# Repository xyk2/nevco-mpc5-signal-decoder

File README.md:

### Extended documentation at https://xy-kao.com/projects/reverse-engineering-a-serial-scoreboard-protocol-nevco-mpc-5/

### Folders
- *`atmega328_MPC_5_signal_generator`* - replicates a signal from the MPC-5
- *`attiny85_multivibrator`* - microcontroller based multivibrator (1MHz)
- *`logic_analyzer_vcd_dumps`* - dumps from the logic analyzer, used to find correct bit positions in bitstream
- *`MPC-5_decoder_schematic`* - schematic diagram for the circuitry
- *`oscilloscope_screenshots`* - screenshots from the oscilloscope
- *`teensy_decoder`* - primary microcontroller to interpret bitstream and send over serial to computer

I have decoded the [Daktronics scoreboard signal](https://xy-kao.com/projects/decoding-daktronics-omnisport-2000/ | width=100) in the past for a swim meet, but this time it's a Nevco MPC-5 multipurpose controller for a basketball. This was considerably more difficult to reverse engineer for several reasons:

- The Daktronics is standard RS232, the MPC-5 runs a non-standard signal
- The MPC-5 sends all scoreboard information over a single coaxial cable
- The clock rate is significantly higher. Daktronics is at 19200 baud (19.2 KHz), the MPC-5 at ~260 KHz
- I had less time with the actual controller to play around with

## Physical layer
The raw signal from the NPC-5 on the oscilloscope looks like this:

So the signal is ~5Vpp ~262KHz, which is a little off from the standard 256KHz for RS232. There also isn't a stop bit. There aren't many serial protocols at this frequency that run on coaxial cable, and the ones I have used before (DMX, RS232/485, CAN bus, I2C, SPI) do not match the signal or cabling, so some more research needed to be done.

After some research, it looks like this signal is a variation of the [1-Wire protocol](https://en.wikipedia.org/wiki/1-Wire), possibly inverted. Some more analysis with the logic analyzer:

I have added annotations to where I deduced the bits are. I have made the assumption that all bits start on the rising-edge. 1-Wire specification says it starts on the falling-edge, but either way, the same bitstream can be read. With the logic analyzer, the following deductions can be made:

- *Start bit* - the start bit is a ~8 microsecond high pulse, followed by a ~0.7 microsecond low pulse
- *1* - a ~3.1 microsecond high pulse is followed by a ~0.7 microsecond low pulse
- *0* - a ~0.7 second high pulse is followed by a ~3.1 microsecond low pulse

The ~3.8 microsecond pulse length gives the signal a ~262KHz data rate, disregarding the start bit. Total of 256 bits are sent (32 bytes) between start pulses.

## Reading the signal
To read this non-standard signal into a microcontroller, I came up with a solution that uses the rising-edges of each bit followed by a delay as a trigger to read the signal. A 0-bit start with a ~0.7us high pulse, so a reading of the signal ~1us later will ensure that a proper reading of 0V is made. Along the same lines, a 1-bit starts with a ~3us high pulse, so a reading 1us after the starting rising-edge will still have a reading of 5V.

A [monostable multivibrator](https://en.wikipedia.org/wiki/Monostable) has the exact functionality required for this - when triggered by a rising-edge from the MPC-5, the multivibrator will output a high 5V for ~1us, after which it returns to a low 0V. That falling-edge can be used as a trigger to read the MPC-5 signal.

Of course, nothing is this ideal in the real world, and after trying the 74LC123 (the standard 74-series multivibrator), I found that it was very difficult to accurately have a 1-2us pulse required for triggering. Standard multivibrators aren't really designed for 1MHz operation - this was confirmed by the datasheet:

A output pulse of 1 microsecond requires a very small capacitance of ~80pF to 800pF, and those are in very ideal conditions. Capacitors tolerances are very wide so a RC pair that is reproducible for a 1 microsecond pulse is very difficult to find.

## Microcontroller multivibrator
To have a reliable ~1 microsecond trigger delay, a ATTiny85 microcontroller (`attiny85_multivibrator`) with a interrupt triggered by the rising-edge was used. The input was the MPC-5 signal, and the two outputs were the trigger pulses, one for the data bits and one for the start bit. A naked ISR specified by `ISR_NAKED` had to be used to speed up the ISR. A custom prologue/epilogue in ASM was added.

Set up the interrupt triggered by a rising edge on the MPC-5 signal:
```c
#if defined (__AVR_ATmega328__)
	EICRA |= (1 << ISC00); // Trigger on rising edge
	EICRA |= (1 << ISC01);
	EIMSK |= (1 << INT0);  // Enable INT0 interrupt vector

#elif defined (__AVR_ATtiny85__)
	MCUCR |= (1 << ISC00); // Trigger on rising edge
	MCUCR |= (1 << ISC01);
	GIMSK |= (1 << INT0);  // Enable INT0 interrupt vector

#endif
```

Interrupt handler for all data bits, outputting a signal to the CLOCK_PULSE pin (PORTB1):
```c
ISR(INT0_vect, ISR_NAKED) {
	asm( // Standard ISR entry, minus "known zero" setup
		"push r0\n"
		"in r0, 0x3F\n"  // Save status
		"push r0" // Might not be needed
	);

	on(CLOCK_PULSE);
	__builtin_avr_delay_cycles(5);
	off(CLOCK_PULSE);

	asm( // low-overhead ISR exit...
		"pop r0\n"  // matches "might not be needed"
		"out 0x3f, r0\n"  // restore status
		"pop r0\n"  // restore r0
		"reti\n"
	);
}
```

A simpler section of code in the main loop detects a high-pulse exceeding ~5us, which means it is must be a start bit so therefore output a pulse to the START_BIT_PULSE pin (PORTB0).

```c
while(1) {
	clocks = 0;

	// Detect start bit - 7us pulse
	while(get(INT0_PIN)) {
		clocks++;

		if(clocks > 4) {
			if(enableInterrupt == 10) {
				on(START_BIT_PULSE); // Send start bit pulse
				out(CLOCK_PULSE); // Enable interrupt clock OUTPUT
				enableInterrupt = 0; // Reset counter
				__builtin_avr_delay_cycles(50);
				off(START_BIT_PULSE);

			} else {
				in(CLOCK_PULSE); // DISABLE interrupt clock OUTPUT
				enableInterrupt++;
			}

			break;
		}
	}
}
```

Note that with a 16MHz crystal clock, each cycle takes 62.5 nanoseconds, however with the added operations before and after `__builtin_avr_delay_cycles()` and ISR interruptions, the delay times were difficult to predict and were done through trial and error on the scope.

The resulting trigger signal from the ATTiny85 looks like this (for data bits), with the yellow the MPC-5 signal and the blue the ATTiny85 trigger signal:

A reading of the MPC-5 (yellow) on every falling-edge of the trigger signal (blue) would yield the correct bit reading.

## Master microcontroller
Now that a trigger edge can be generated with the ATTiny85, another microcontroller is responsible for reading the MPC-5 data on each falling-edge, shuffling it into bytes, then interpreting it to find the actual game clock and shot clock information on the scoreboard.

A Teensy was used for this, as it has a serial port, two interrupts available, and a interval timer. Its operation is similar to the ATTiny85, except that rather than outputting a trigger pulse, it reads the data, interprets it, then sends it along through TTL serial to a computer. Presumably, both microcontroller operations can be done on a single microcontroller, but this solution was easier for me to implement.

```c
static volatile uint16_t bit_index = 0; // Increment this on each CLOCK ISR, reset on START ISR
static volatile uint8_t MPC5_bits[260]; // Holds bitstream for current packet

attachInterrupt(3, ISR_SERVICE_ROUTINE_DATA, RISING);
attachInterrupt(5, ISR_SERVICE_ROUTINE_START, RISING);

static void ISR_SERVICE_ROUTINE_START() {
	bit_index = 0; // Reset index to zero on each trigger edge
}

static void ISR_SERVICE_ROUTINE_DATA() {
	MPC5_bits[bit_index++] = digitalReadFast(6); // Read MPC-5 data from pin 6 into bitstream array
}

```

## Getting the scoreboard data
To interpret the bitstream, a process of trial and error and observation was used. The full 256 bitstream was recorded with the controller set to a score of 0-0 and a clock time of 00:00. Then the controller was set to 0-1 and 00:00, then the complete bitstream recorded again. This goes on for every digit, so a complete set of bitstreams can be recorded.

To find the relevant bits for each scoreboard digit, I looked at the bits that were changing. Eventually, every single digit and its corresponding bit positions was mapped out:

| Digits | Bit Positions
| - | -
| Home team score | 150-153, 166-169
| Away team score | 6-9, 22-25
| Period | 54-57
| Shot clock | 238-240, 222-225
| Minutes | 118-121
| Seconds | 102-105, 86-89

Each digit is 4 bits, encoded with [binary-coded-decimal](https://en.wikipedia.org/wiki/Binary-coded_decimal). A simple function converts the BCD bits to a decimal value:

```c
static uint8_t bcd_to_decimal(uint8_t bit1, uint8_t bit2, uint8_t bit3, uint8_t bit4) {
	uint8_t sum = 0;
	if(bit1) sum += 0b0001;
	if(bit2) sum += 0b0010;
	if(bit3) sum += 0b0100;
	if(bit4) sum += 0b1000;

	if(sum > 9) return 0;
	return sum;
}
```

Once all the digits are read from the bitstream, it is sent down the serial port every 100ms with the Teensy Metro library to a computer to generate the graphics.

## Circuitry
Nothing special for the circuitry apart from a 5V-3.3V logic level converter and a 50 ohm termination. The MPC-5 signal is 5Vpp so it is shifted down to 3.3Vpp for the Teensy.

## MPC-5 simulator
To test the decoder without having the actual MPC-5 controller, I coded a simple signal generator that reproduces the signal to specifications (5Vpp, ~260KHz, valid bitstream). This is in the `atmega328_MPC_5_signal_generator` folder.

## Code
Code is published on GitHub at [nevco-mpc5-signal-decoder](https://github.com/xyk2/Scoreboard-webcam-OCR).

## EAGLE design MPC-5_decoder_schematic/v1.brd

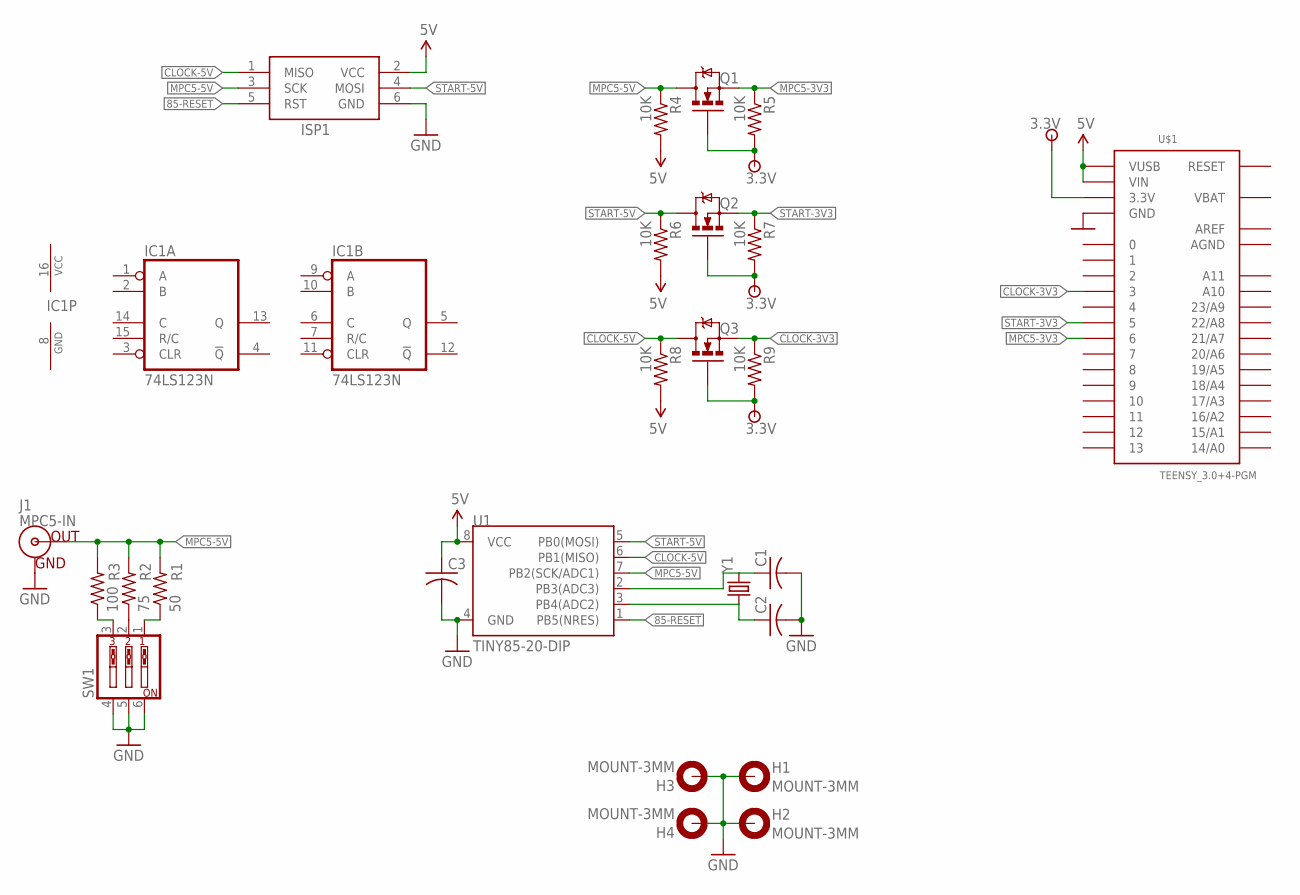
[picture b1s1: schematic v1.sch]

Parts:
C1, C2, C3: C-USNEWSILK; C0805K
H1, H2, H3, H4: MOUNT-3MM; 3,0-PAD
IC1: 74LS123N; DIL16
ISP1: AVRISP-6; AVRISP
J1: MPC5-IN; BNC
Q1, Q2, Q3: BSS138; SOT23
R1: 50; R0805
R2: 75; R0805
R3: 100; R0805
R4, R5, R6, R7, R8, R9: 10K; R0805
SW1: SW_DIP-3; EDG-03
U1: TINY85-20-DIP; DIP08
U$1: TEENSY_3.0+4-PGM
Y1: CRYSTALHC49UV; HC49U-V

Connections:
3.3V: Q1.1 (G), Q2.1 (G), Q3.1 (G), R5.2, R7.2, R9.2, U$1.3.3V, U$1.3.3V1 (3.3V)
5V: C3.1, ISP1.2 (VCC), R4.2, R6.2, R8.2, U1.8 (VCC), U$1.VIN, U$1.VUSB
85-RESET: ISP1.5 (RST), U1.1 (PB5(NRES))
AGND: U$1.AGND
AREF: U$1.AREF
CLOCK-3V3: Q3.2 (S), R9.1, U$1.3
CLOCK-5V: ISP1.1 (MISO), Q3.3 (D), R8.1, U1.6 (PB1(MISO))
GND: C1.2, C2.2, C3.2, H1.B3,0, H2.B3,0, H3.B3,0, H4.B3,0, IC1.8 (GND), ISP1.6 (GND), J1.GND, SW1.4, SW1.5, SW1.6, U1.4 (GND), U$1.GND, U$1.GND1 (GND)
MPC5-3V3: Q1.2 (S), R5.1, U$1.6
MPC5-5V: ISP1.3 (SCK), J1.S (OUT), Q1.3 (D), R1.2, R2.2, R3.2, R4.1, U1.7 (PB2(SCK/ADC1))
unnamed: R1.1, SW1.1
unnamed: R2.1, SW1.2
unnamed: R3.1, SW1.3
unnamed: C1.1, U1.2 (PB3(ADC3)), Y1.2
unnamed: C2.1, U1.3 (PB4(ADC2)), Y1.1
START-3V3: Q2.2 (S), R7.1, U$1.5
START-5V: ISP1.4 (MOSI), Q2.3 (D), R6.1, U1.5 (PB0(MOSI))
VBAT: U$1.VBAT
VCC: IC1.16 (VCC)

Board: 2 copper layers, 26 parts (0 on the bottom side), 15 nets, no tracks yet.

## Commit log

2018-10-13 Intial commit

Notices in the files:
parts and their libraries:
SparkFun-Connectors: Licensing: CC v3.0 Share-Alike You are welcome to use this library for commercial purposes.
